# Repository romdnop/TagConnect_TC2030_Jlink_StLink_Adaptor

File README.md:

# About

TagConnect TC2030 to Jlink/StLink adaptor

# Pictures

# Fabrication files

## V1 (16.08.2026)

Changelog:

- First version

Fabrication files: [TC2030_St-Link_V2_Adapter_2026-08-16_Production_Files.zip](output/TC2030_St-Link_V2_Adapter_2026-08-16_Production_Files.zip)

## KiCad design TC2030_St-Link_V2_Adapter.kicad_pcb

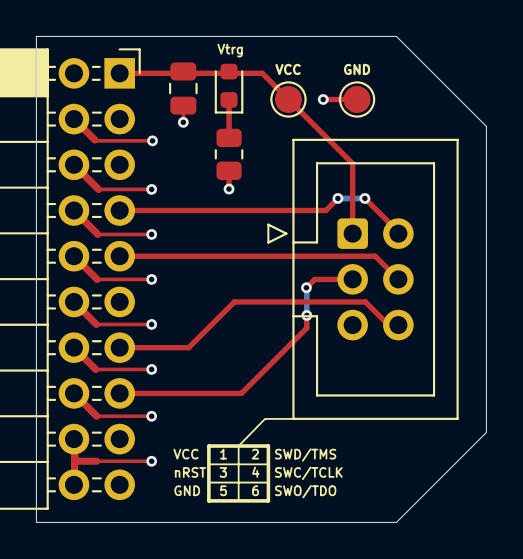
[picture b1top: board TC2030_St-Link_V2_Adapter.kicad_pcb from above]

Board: 2 copper layers, 25.0 x 27.0 mm, 7 parts (0 on the bottom side), 7 nets.

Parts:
C1: 0.1; C_0805_2012Metric
D1: RED; D_0603_1608Metric
GND: TP2; TestPoint_Pad_D1.5mm
J1: Conn_02x10_Odd_Even; PinSocket_2x10_P2.54mm_Horizontal
J3: Conn_02x03_Odd_Even; IDC-Header_2x03_P2.54mm_Vertical
R1: 470; R_0805_2012Metric
VCC: TP1; TestPoint_Pad_D1.5mm

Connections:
/SWC/TCLK: J1.9, J3.4
/SWDIO/TMS: J1.7, J3.2
/SWO/TDO: J1.13, J3.6
/nRESET: J1.15, J3.3
GND: C1.2, GND.1, J1.4, J1.6, J1.8, J1.10, J1.12, J1.14, J1.16, J1.18, J1.20, J3.5, R1.2
unnamed: D1.1 (K), R1.1
VCC: C1.1, D1.2 (A), J1.1, J3.1, VCC.1
